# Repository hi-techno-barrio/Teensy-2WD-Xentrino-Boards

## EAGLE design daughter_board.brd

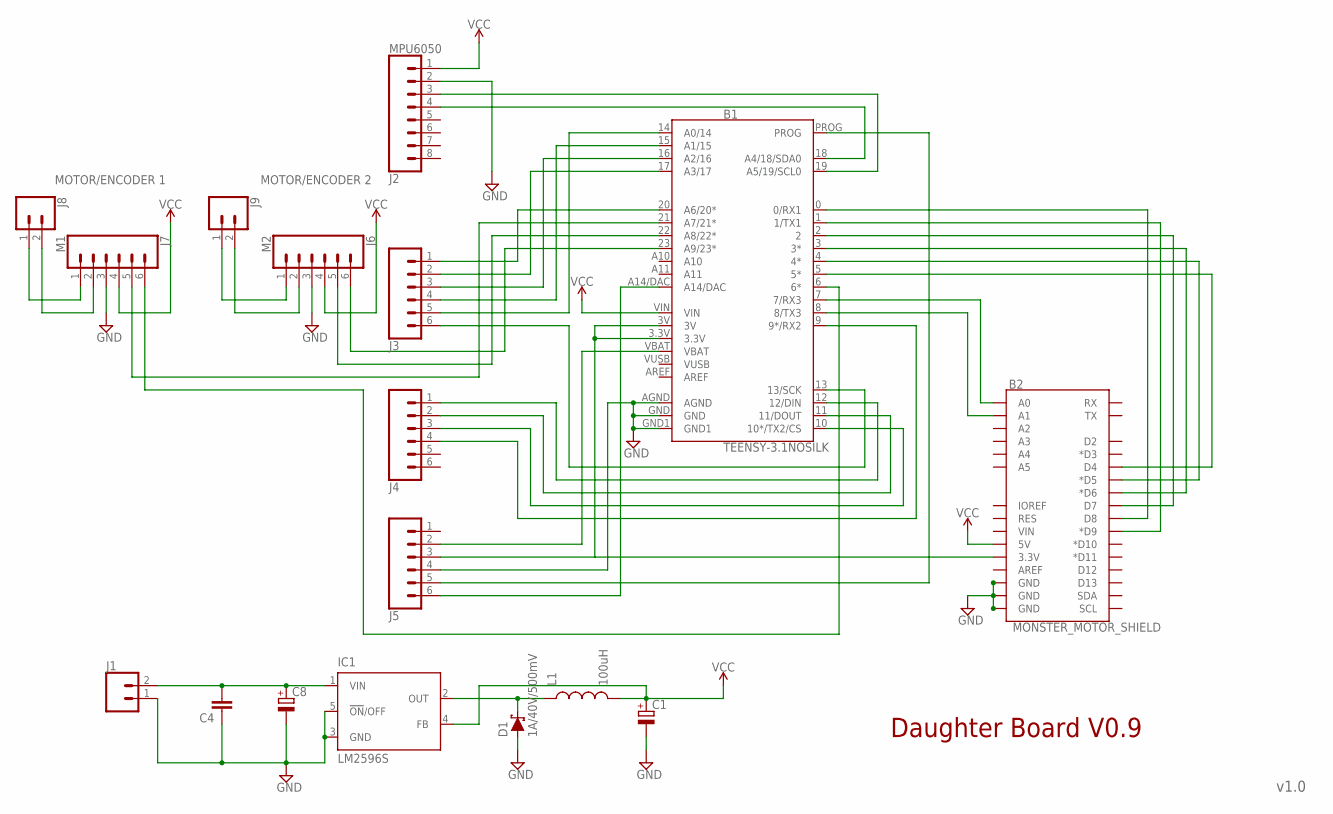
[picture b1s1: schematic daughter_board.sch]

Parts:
B1: TEENSY-3.1NOSILK; TEENSY-3.1_NOSILK
B2: MONSTER_MOTOR_SHIELD; UNO_R3_SHIELD_NOLABELS
C1, C8: CPOL-EU150CLZ-0810; 150CLZ-0810
C4: C-EUC0805; C0805
D1: 1A/40V/500mV; SMA-DIODE
IC1: LM2596S; TO263-5
J1, J8, J9: CONN_023.5MM-NO_SILK; SCREWTERMINAL-3.5MM-2-NS
J2: MPU6050; 1X08_NO_SILK
J3, J4, J5: CONN_06NO_SILK_FEMALE_PTH; 1X06_NO_SILK
J6: M2; 1X06_NO_SILK
J7: M1; 1X06_NO_SILK
L1: 100uH; CDRH125

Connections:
GND: B1.AGND, B1.GND, B1.GND1, B2.GND@0 (GND), B2.GND@1 (GND), B2.GND@2 (GND), C1.-, C4.1, C8.-, D1.A, IC1.3 (GND), IC1.5 (!ON!/OFF), J1.1, J2.2, J5.4, J6.3, J7.3
unnamed: B1.19 (A5/19/SCL0), J2.3
unnamed: B1.18 (A4/18/SDA0), J2.4
unnamed: B1.20 (A6/20*), J3.1
unnamed: B1.17 (A3/17), J3.2
unnamed: B1.16 (A2/16), J3.3
unnamed: B1.15 (A1/15), J3.4
unnamed: B1.14 (A0/14), J3.5
unnamed: B1.13 (13/SCK), J3.6
unnamed: B1.12 (12/DIN), J4.1
unnamed: B1.11 (11/DOUT), J4.2
unnamed: B1.10 (10*/TX2/CS), J4.3
unnamed: B1.9 (9*/RX2), J4.4
unnamed: B1.VBAT, J5.2
unnamed: C4.2, C8.+, IC1.1 (VIN), J1.2
unnamed: B1.PROG, J5.5
unnamed: B1.A14/DAC, J5.6
unnamed: B1.0 (0/RX1), B2.D8
unnamed: B1.1 (1/TX1), B2.D9 (*D9)
unnamed: B1.2, B2.D7
unnamed: B1.3 (3*), B2.D6 (*D6)
unnamed: B1.4 (4*), B2.D5 (*D5)
unnamed: B1.5 (5*), B2.D4
unnamed: B1.7 (7/RX3), B2.A0
unnamed: B1.8 (8/TX3), B2.A1
unnamed: J7.1, J8.1
unnamed: J7.2, J8.2
unnamed: J6.1, J9.1
unnamed: J6.2, J9.2
unnamed: B1.3.3V, B1.3V, B2.3.3V, J5.3
unnamed: D1.C, IC1.2 (OUT), L1.1
unnamed: B1.23 (A9/23*), J6.6
unnamed: B1.22 (A8/22*), J6.5
unnamed: B1.21 (A7/21*), J7.5
unnamed: B1.6 (6*), J7.6
VCC: B1.VIN, B2.5V, C1.+, IC1.4 (FB), J2.1, J6.4, J7.4, L1.2
VUSB: B1.VUSB

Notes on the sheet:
v1.0
Daughter Board V0.9
MOTOR/ENCODER 1
MOTOR/ENCODER 2

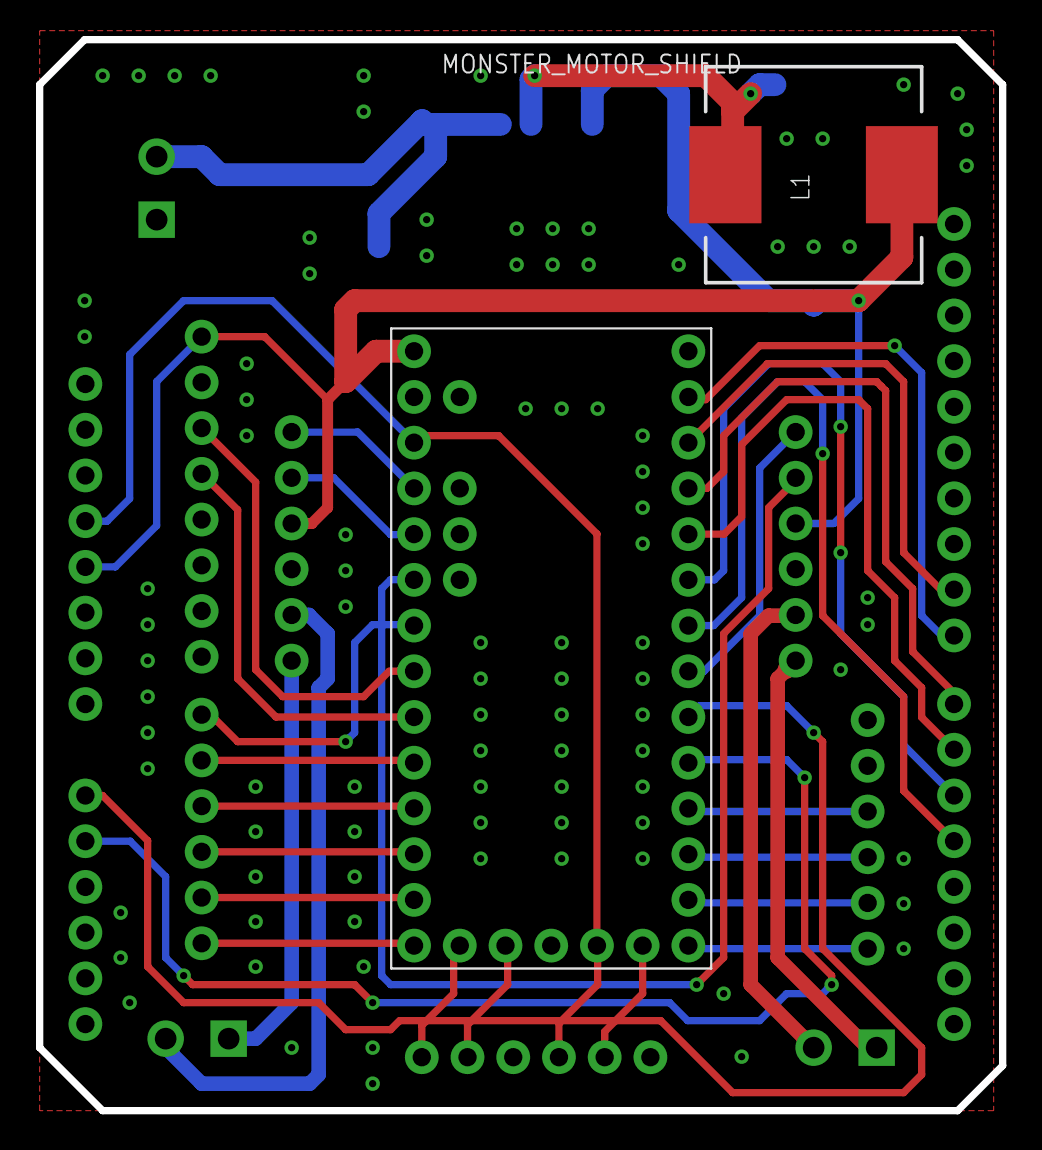
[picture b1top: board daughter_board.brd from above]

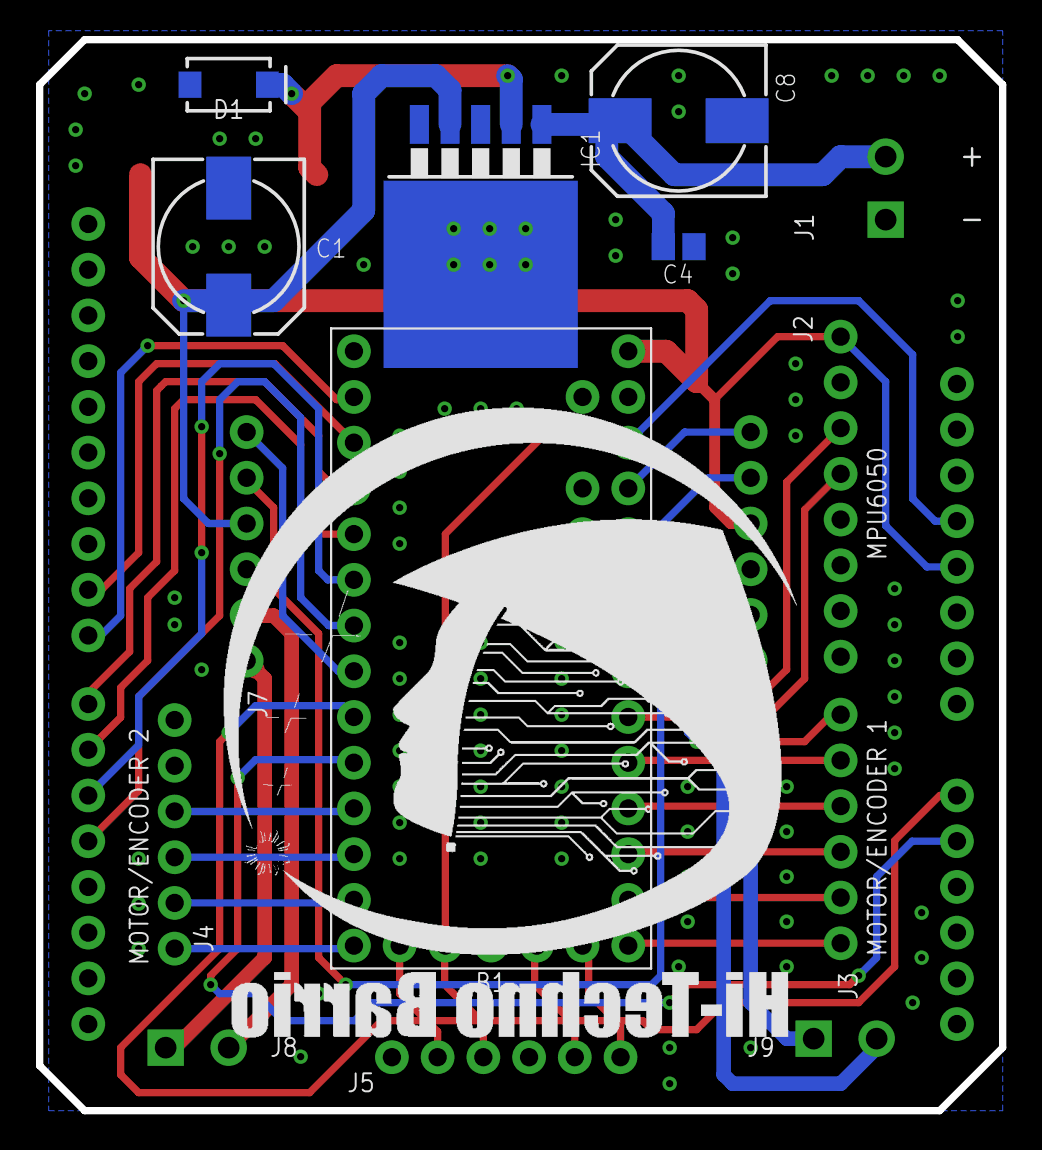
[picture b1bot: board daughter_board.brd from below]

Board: 2 copper layers, 53.5 x 59.5 mm, 17 parts (9 on the bottom side), 36 nets.

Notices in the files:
parts and their libraries:
SparkFun-Connectors: Licensing: Creative Commons ShareAlike 4.0 International - https://creativecommons.org/licenses/by-sa/4.0
